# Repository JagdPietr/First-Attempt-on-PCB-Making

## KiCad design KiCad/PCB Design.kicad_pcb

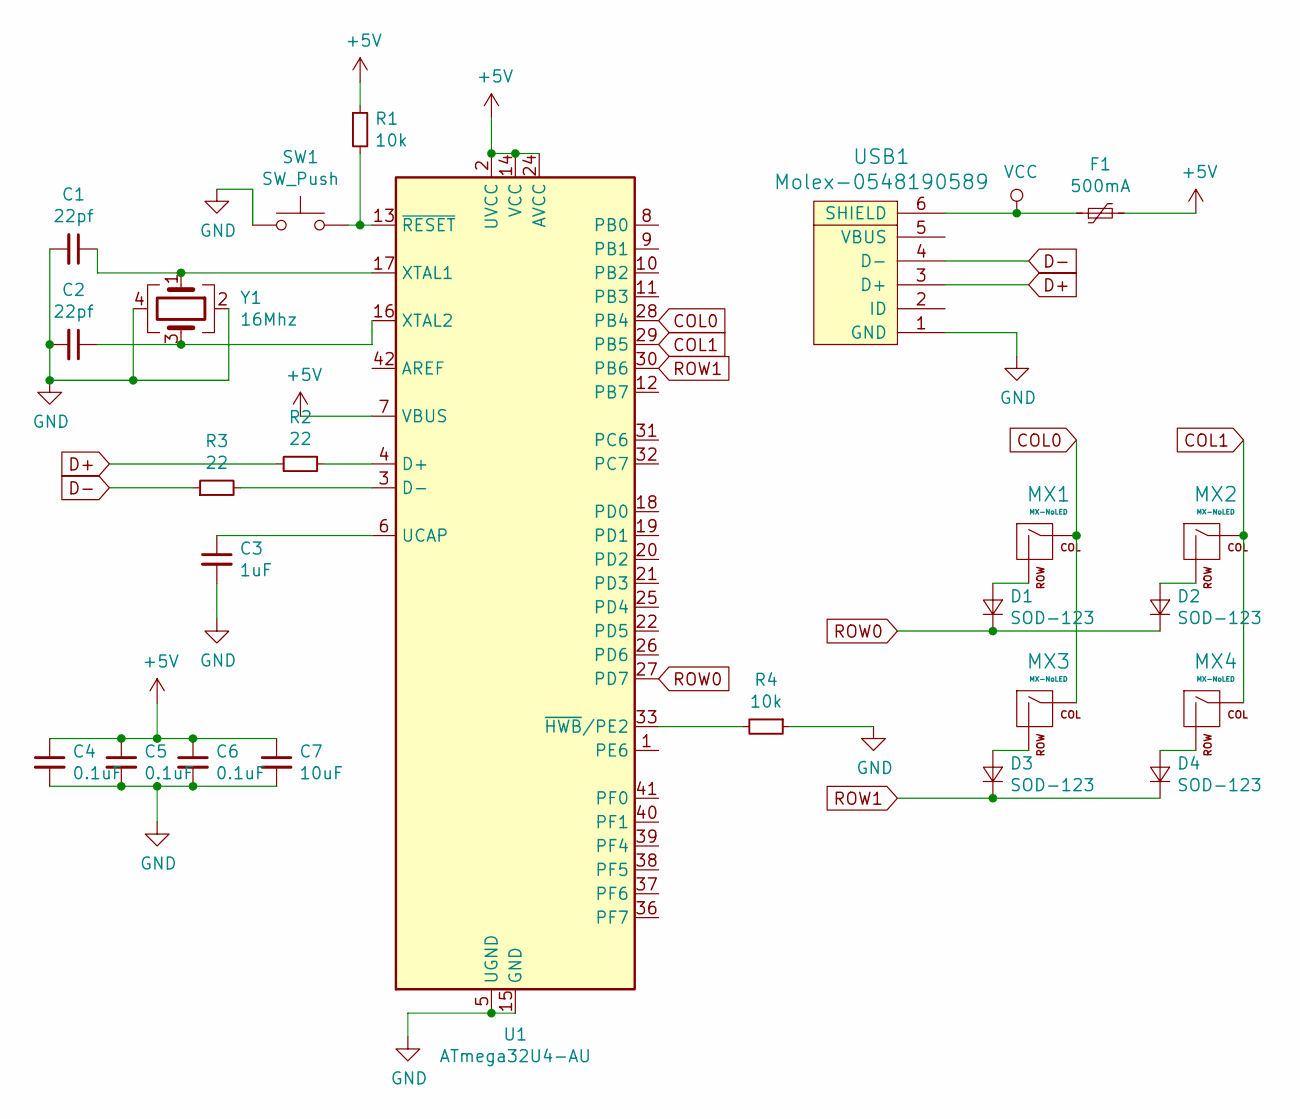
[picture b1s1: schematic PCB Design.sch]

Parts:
C1, C2: 22pf; C_0805_2012Metric
C3: 1uF; C_0805_2012Metric
C4, C5, C6: 0.1uF; C_0805_2012Metric
C7: 10uF; C_0805_2012Metric
D1, D2, D3, D4: SOD-123; D_SOD-123
F1: 500mA; Fuse_1206_3216Metric
MX1, MX2, MX3, MX4: MX-NoLED; MXOnly-1U-NoLED
R1, R4: 10k; R_0805_2012Metric
R2, R3: 22; R_0805_2012Metric
SW1: SW_Push; SKQG-1155865
U1: ATmega32U4-AU; TQFP-44_10x10mm_P0.8mm
USB1: Molex-0548190589
Y1: 16Mhz; Crystal_SMD_3225-4Pin_3.2x2.5mm

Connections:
+5V: C4.1, C5.1, C6.1, C7.1, F1.2, R1.1, U1.2 (UVCC), U1.7 (VBUS), U1.14 (VCC), U1.24 (AVCC), U1.34 (VCC), U1.44 (AVCC)
COL0: MX1.1 (COL), MX3.1 (COL), U1.28 (PB4)
COL1: MX2.1 (COL), MX4.1 (COL), U1.29 (PB5)
D+: R2.1, USB1.3 (D+)
D-: R3.1, USB1.4 (D-)
GND: C1.2, C2.2, C3.2, C4.2, C5.2, C6.2, C7.2, R4.1, SW1.1, U1.5 (UGND), U1.15 (GND), U1.23 (GND), U1.35 (GND), U1.43 (GND), USB1.1 (GND), Y1.2, Y1.4
unnamed: C1.1, U1.17 (XTAL1), Y1.1
unnamed: C2.1, U1.16 (XTAL2), Y1.3
unnamed: C3.1, U1.6 (UCAP)
unnamed: D1.2 (A), MX1.2 (ROW)
unnamed: D2.2 (A), MX2.2 (ROW)
unnamed: D3.2 (A), MX3.2 (ROW)
unnamed: D4.2 (A), MX4.2 (ROW)
unnamed: R1.2, SW1.2, U1.13 (~RESET)
unnamed: R2.2, U1.4 (D+)
unnamed: R3.2, U1.3 (D-)
unnamed: R4.2, U1.33 (~HWB~/PE2)
ROW0: D1.1 (K), D2.1 (K), U1.27 (PD7)
ROW1: D3.1 (K), D4.1 (K), U1.30 (PB6)
VCC: F1.1, USB1.6 (SHIELD)

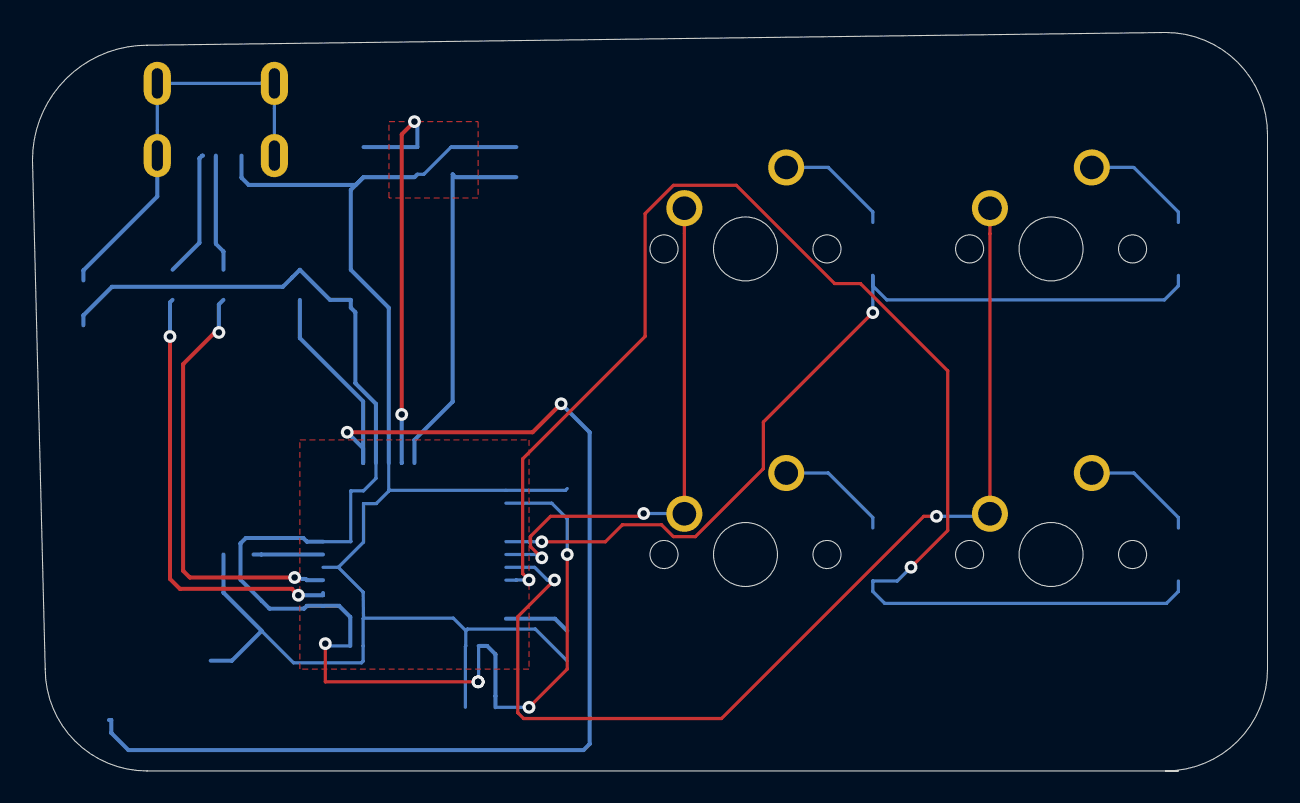
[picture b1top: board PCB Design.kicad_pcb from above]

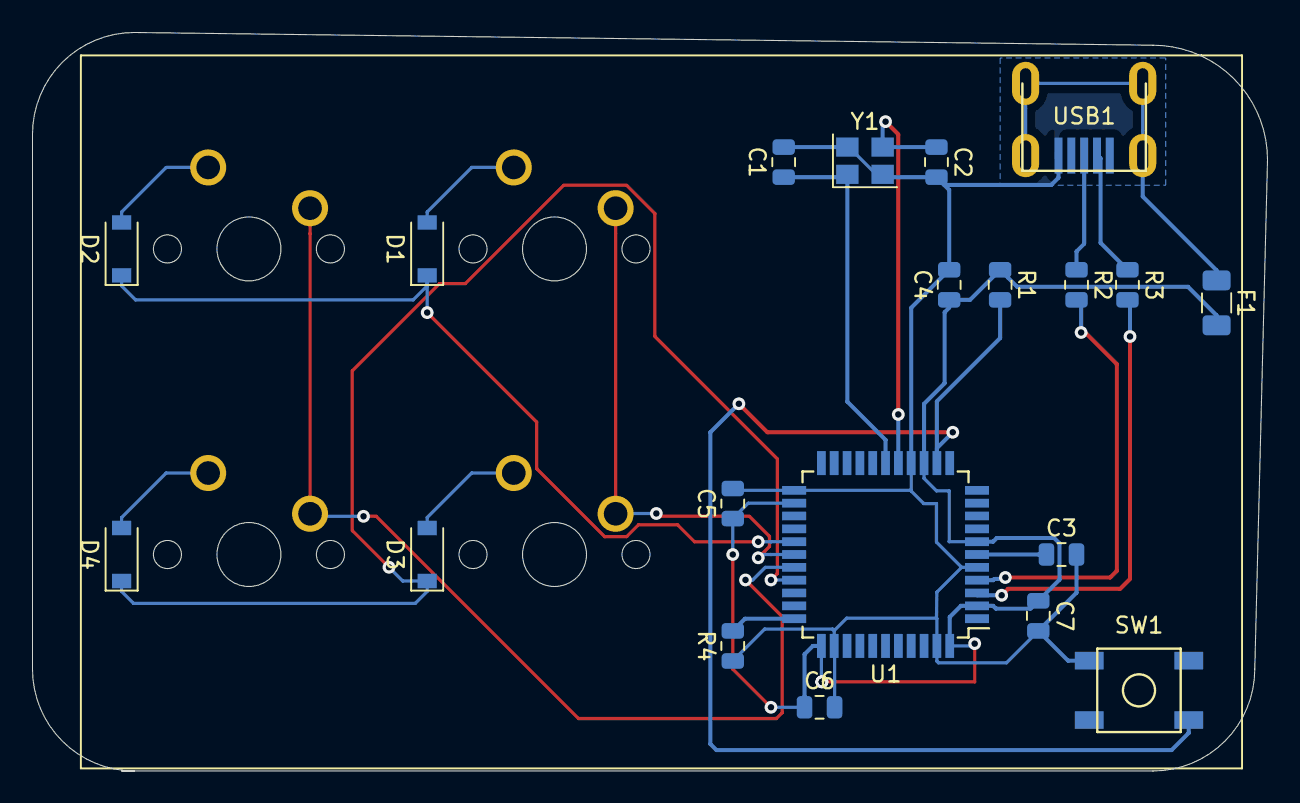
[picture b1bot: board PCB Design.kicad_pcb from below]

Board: 2 copper layers, 77.0 x 46.0 mm, 24 parts (20 on the bottom side), 20 nets.

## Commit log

2020-03-20 First entry to kb PCB designing
2020-03-20 Parts
2020-03-20 Libraries
2020-03-20 Schematic Layout
2020-03-20 MX Edits
2020-03-20 History
2020-03-20 Progress
2020-03-21 Edits
2020-03-21 Routing
2020-03-21 Finalization
2020-03-21 Finalized
